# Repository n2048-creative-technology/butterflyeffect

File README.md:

# butterflyeffect

An art-installation project built around small ESP32-S3 "leaf" PCBs: each
leaf carries a radar presence sensor and a TFT display that reacts with a
glitch/text effect. Includes the PCB design (KiCad, three board revisions),
two firmware variants, and a source poem ("poetry monitors butterfly.pdf")
that the TFT glitch text is drawn from.

**Status: messy / in-progress.** This repo is committed close to how it sits
on the author's disk — see "Known issues" below before relying on it as a
clean starting point.

## What's in here

- **`PCB/leaf/`, `PCB/leaf2/`, `PCB/leaf3/`** — three KiCad project revisions
  for the same "leaf" board (ESP32-S6/S3 module, per `esp32-s3-leaf.kicad_sch`
  at the repo root). `leaf3` is the newest revision judging by file
  timestamps; `leaf`/`leaf2` look like earlier iterations kept for reference.
  Each folder also has a `production/` subfolder with JLCPCB-ready gerbers,
  BOM and pick-and-place files, plus a `*-backups/` folder full of
  auto-save zips from KiCad — safe to ignore/delete, not source files.
- **`esp32-s3/`** — a fourth, separate KiCad PCB export (gerbers + production
  files only, no schematic source committed alongside it) — likely an older
  or alternate board revision. Not clearly connected to `PCB/leaf*` from the
  file layout alone.
- **`code/esp32-s3-radar-test/`** — PlatformIO project reading an RD-03D
  mmWave presence/distance radar module over UART (`RD03D.h/.cpp`).
- **`code/esp32-s3-tft-display/`** — PlatformIO project driving a TFT
  display (via `TFT_eSPI`) with a scrolling/glitching text effect —
  `GLITCH_PERCENT`, `FRAME_DELAY_MS`, and the displayed text are `#define`d
  at the top of `leafs/src/main.cpp` and `code/esp32-s3-tft-display/src/main.cpp`.
  Uses a RAM-framebuffer sprite for performance (see the comment block in
  `main.cpp` explaining why).
- **`leafs/`** — a third, PlatformIO-structured copy of the TFT glitch
  firmware (`include/User_Setup.h` for `TFT_eSPI` pin config). Appears to be
  the "current" leaf firmware; unclear how it differs from
  `code/esp32-s3-tft-display/` without a diff.
- **`3dmodels/wings.scad`** — OpenSCAD source for a mechanical "wings" part.
- **`poetry monitors butterfly.pdf`** — the source text the glitch display
  renders excerpts of.

## Hardware

- ESP32-S3 module (per `esp32-s3-leaf.kicad_sch` / the `leaf` PCB silkscreen)
- RD-03D mmWave radar module (UART, 256000 baud) for the radar-test firmware
- A TFT display wired for `TFT_eSPI` (pinout is in `leafs/include/User_Setup.h`
  — check it before wiring a display, it is not documented here separately)
- Custom "leaf" PCB (KiCad projects above) carrying the ESP32-S3 and
  supporting components

No end-to-end wiring diagram tying the radar + display + leaf PCB into one
finished device exists in this repo — piece it together from the two
firmware projects' pin `#define`s and the KiCad schematic.

## Build & flash

Both firmware projects use PlatformIO:

```bash
cd code/esp32-s3-radar-test   # or code/esp32-s3-tft-display, or leafs/
pio run
pio run -t upload
pio device monitor
```

## Known issues

- **Three near-duplicate PCB revisions** (`PCB/leaf`, `PCB/leaf2`, `PCB/leaf3`)
  and a fourth unrelated-looking one (`esp32-s3/`) are committed side by
  side with no changelog explaining what changed between them. Before
  fabricating, diff the schematics or ask the author which is current
  (`leaf3` is the most recently modified).
- **KiCad auto-save backup zips are committed** (`*-backups/*.zip`, dozens
  of them, several MB each) — these bloat the repo and aren't needed to
  build the board; the checked-in `.kicad_pcb`/`.kicad_sch` files are the
  actual source of truth.
- **Two copies of the TFT glitch firmware** (`code/esp32-s3-tft-display/`
  and `leafs/`) with no documented relationship between them.
- No top-level wiring diagram or bill of materials tying the radar sensor,
  display, and PCB together into one buildable device.

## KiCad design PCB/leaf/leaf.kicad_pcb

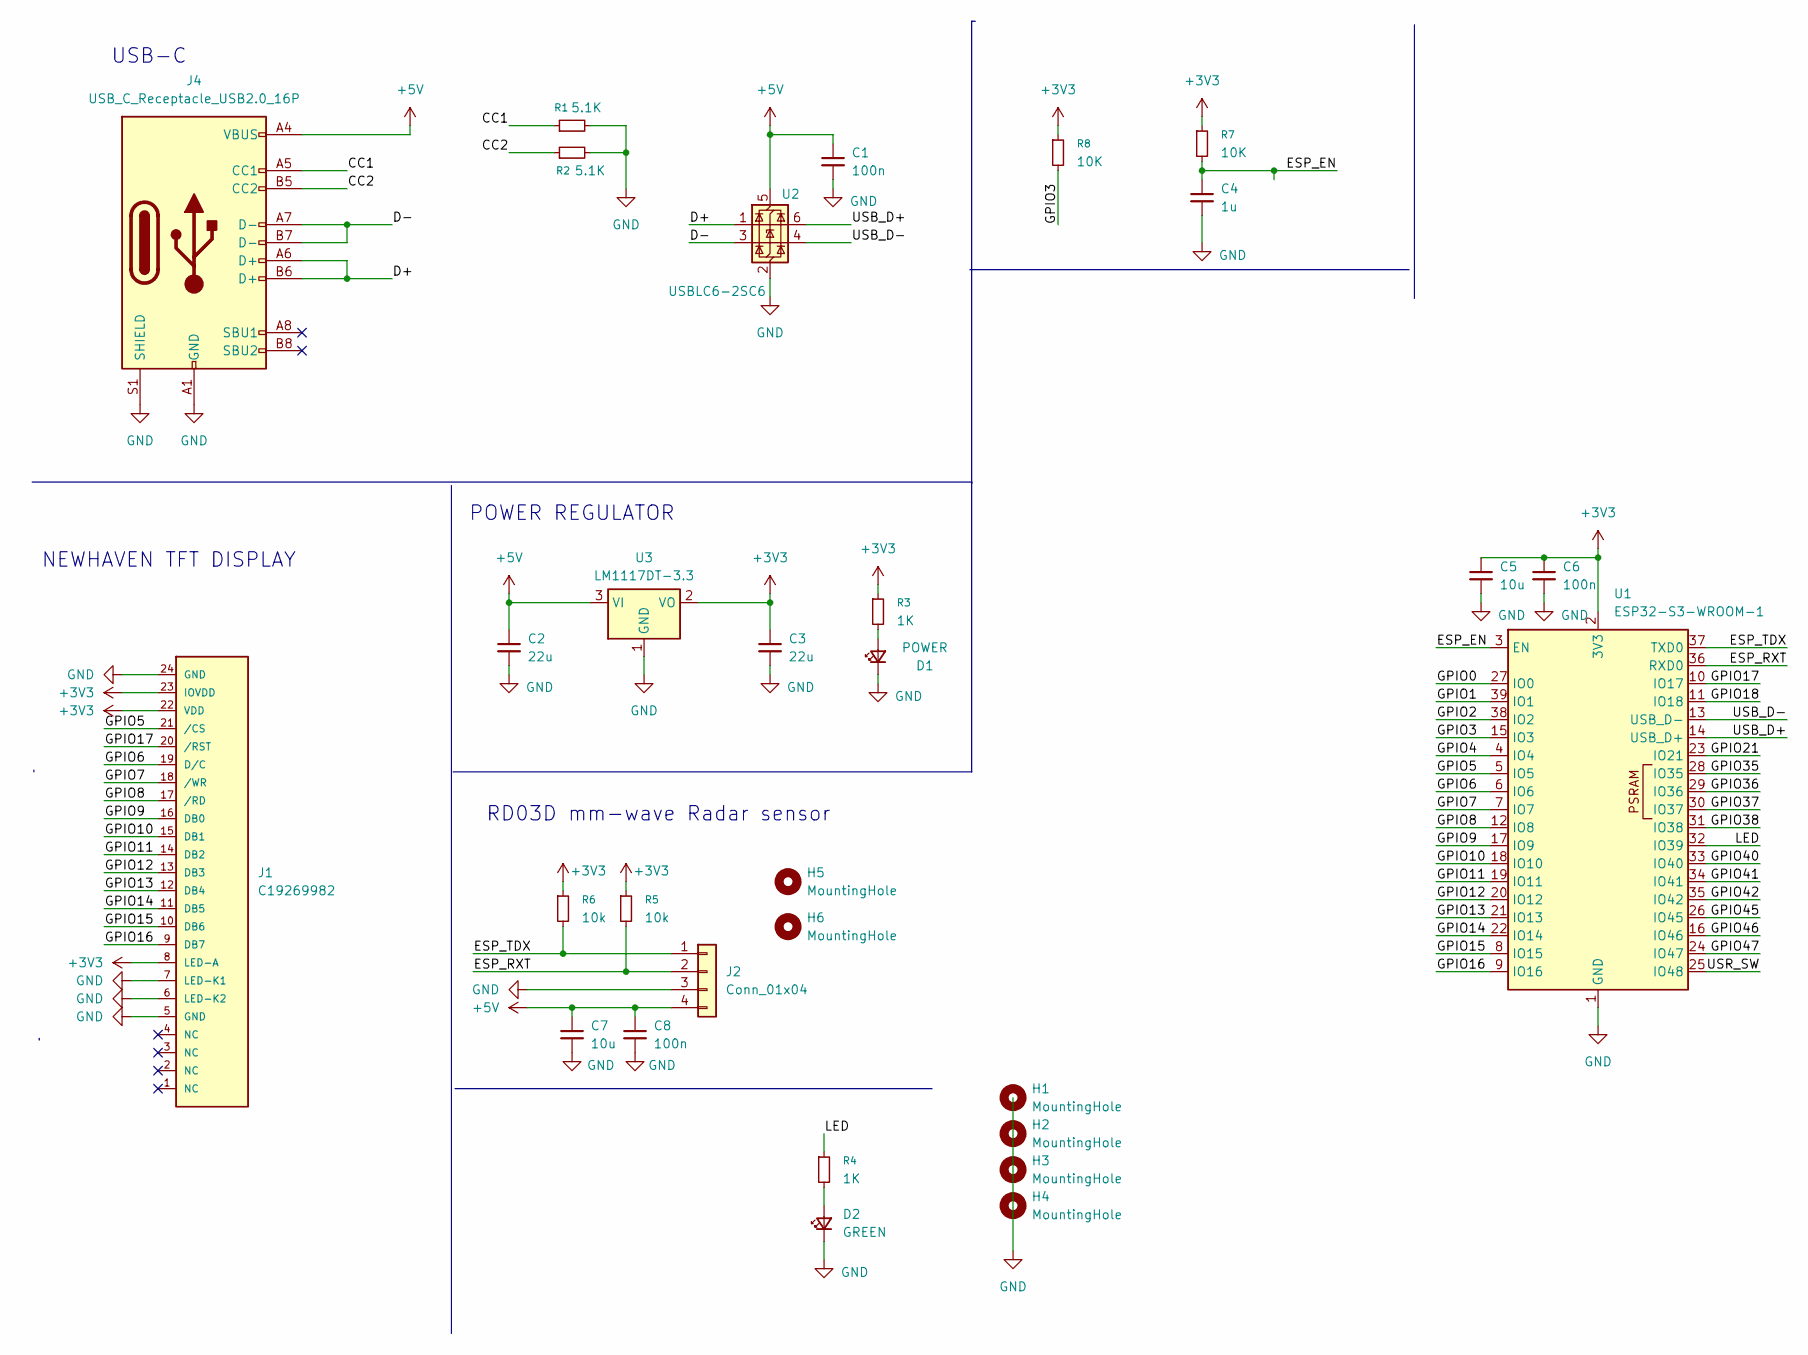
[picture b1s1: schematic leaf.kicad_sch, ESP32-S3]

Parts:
C1, C6, C8: 100n; C_01005_0402Metric_Pad0.57x0.30mm_HandSolder
C2, C3: 22u; C_1210_3225Metric
C4: 1u; C_0603_1608Metric
C5, C7: 10u; C_0603_1608Metric
D1: POWER; LED_0603_1608Metric
D2: GREEN; LED_0603_1608Metric
H1, H2, H3, H4: MountingHole; MountingHole_4.3mm_M4_ISO14580_Pad
H5, H6: MountingHole; MountingHole_2.2mm_M2_ISO7380_Pad
J1: C19269982; Molex_502244-2430_1x24-1MP_P0.5mm_Horizontal
J2: Conn_01x04; Molex_PicoBlade_53261-0471_1x04-1MP_P1.25mm_Horizontal
J4: USB_C_Receptacle_USB2.0_16P; USB_C_Receptacle_GCT_USB4105-xx-A_16P_TopMnt_Horizontal
R1, R2: 5.1K; R_0402_1005Metric_Pad0.72x0.64mm_HandSolder
R3, R4: 1K; R_0402_1005Metric_Pad0.72x0.64mm_HandSolder
R5, R6: 10k; R_0402_1005Metric_Pad0.72x0.64mm_HandSolder
R7, R8: 10K; R_0402_1005Metric_Pad0.72x0.64mm_HandSolder
U1: ESP32-S3-WROOM-1
U2: USBLC6-2SC6; SOT-23-6
U3: LM1117DT-3.3; TO-252-3_TabPin2

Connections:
+3V3: C3.1, C5.1, C6.1, J1.8 (LED-A), J1.22 (VDD), J1.23 (IOVDD), R3.1, R5.1, R6.1, R7.1, R8.1, U1.2 (3V3), U3.2 (VO)
+5V: C1.1, C2.1, C7.1, C8.1, J2.4, J4.A4 (VBUS), J4.A9 (VBUS), J4.B4 (VBUS), J4.B9 (VBUS), U2.5 (VBUS), U3.3 (VI)
/CC1: J4.A5 (CC1), R1.1
/CC2: J4.B5 (CC2), R2.1
/D+: J4.A6 (D+), J4.B6 (D+), U2.1 (I/O1)
/D-: J4.A7 (D-), J4.B7 (D-), U2.3 (I/O2)
/ESP_EN: C4.1, R7.2, U1.3 (EN)
/ESP_RXT: J2.2, R5.2, U1.36 (RXD0)
/ESP_TDX: J2.1, R6.2, U1.37 (TXD0)
/GPIO0: U1.27 (IO0)
/GPIO1: U1.39 (IO1)
/GPIO2: U1.38 (IO2)
/GPIO3: R8.2, U1.15 (IO3)
/GPIO4: U1.4 (IO4)
/GPIO5: J1.21 (/CS), U1.5 (IO5)
/GPIO6: J1.19 (D/C), U1.6 (IO6)
/GPIO7: J1.18 (/WR), U1.7 (IO7)
/GPIO8: J1.17 (/RD), U1.12 (IO8)
/GPIO9: J1.16 (DB0), U1.17 (IO9)
/GPIO10: J1.15 (DB1), U1.18 (IO10)
/GPIO11: J1.14 (DB2), U1.19 (IO11)
/GPIO12: J1.13 (DB3), U1.20 (IO12)
/GPIO13: J1.12 (DB4), U1.21 (IO13)
/GPIO14: J1.11 (DB5), U1.22 (IO14)
/GPIO15: J1.10 (DB6), U1.8 (IO15)
/GPIO16: J1.9 (DB7), U1.9 (IO16)
/GPIO17: J1.20 (/RST), U1.10 (IO17)
/GPIO18: U1.11 (IO18)
/GPIO21: U1.23 (IO21)
/GPIO35: U1.28 (IO35)
/GPIO36: U1.29 (IO36)
/GPIO37: U1.30 (IO37)
/GPIO38: U1.31 (IO38)
/GPIO40: U1.33 (IO40)
/GPIO41: U1.34 (IO41)
/GPIO42: U1.35 (IO42)
/GPIO45: U1.26 (IO45)
/GPIO46: U1.16 (IO46)
/GPIO47: U1.24 (IO47)
/LED: R4.1, U1.32 (IO39)
/USB_D+: U1.14 (USB_D+), U2.6 (I/O1)
/USB_D-: U1.13 (USB_D-), U2.4 (I/O2)
/USR_SW: U1.25 (IO48)
GND: C1.2, C2.2, C3.2, C4.2, C5.2, C6.2, C7.2, C8.2, D1.1 (K), D2.1 (K), J1.5 (GND), J1.6 (LED-K2), J1.7 (LED-K1), J1.24 (GND), J1.MP, J2.3, J2.MP, J4.A1 (GND), J4.A12 (GND), J4.B1 (GND), J4.B12 (GND), J4.S1 (SHIELD), R1.2, R2.2, U1.1 (GND), U1.40 (GND), U1.41 (GND), U2.2 (GND), U3.1 (GND)
unnamed: D1.2 (A), R3.2
unnamed: D2.2 (A), R4.2

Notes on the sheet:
NEWHAVEN TFT DISPLAY
USB-C
POWER REGULATOR
RD03D mm-wave Radar sensor

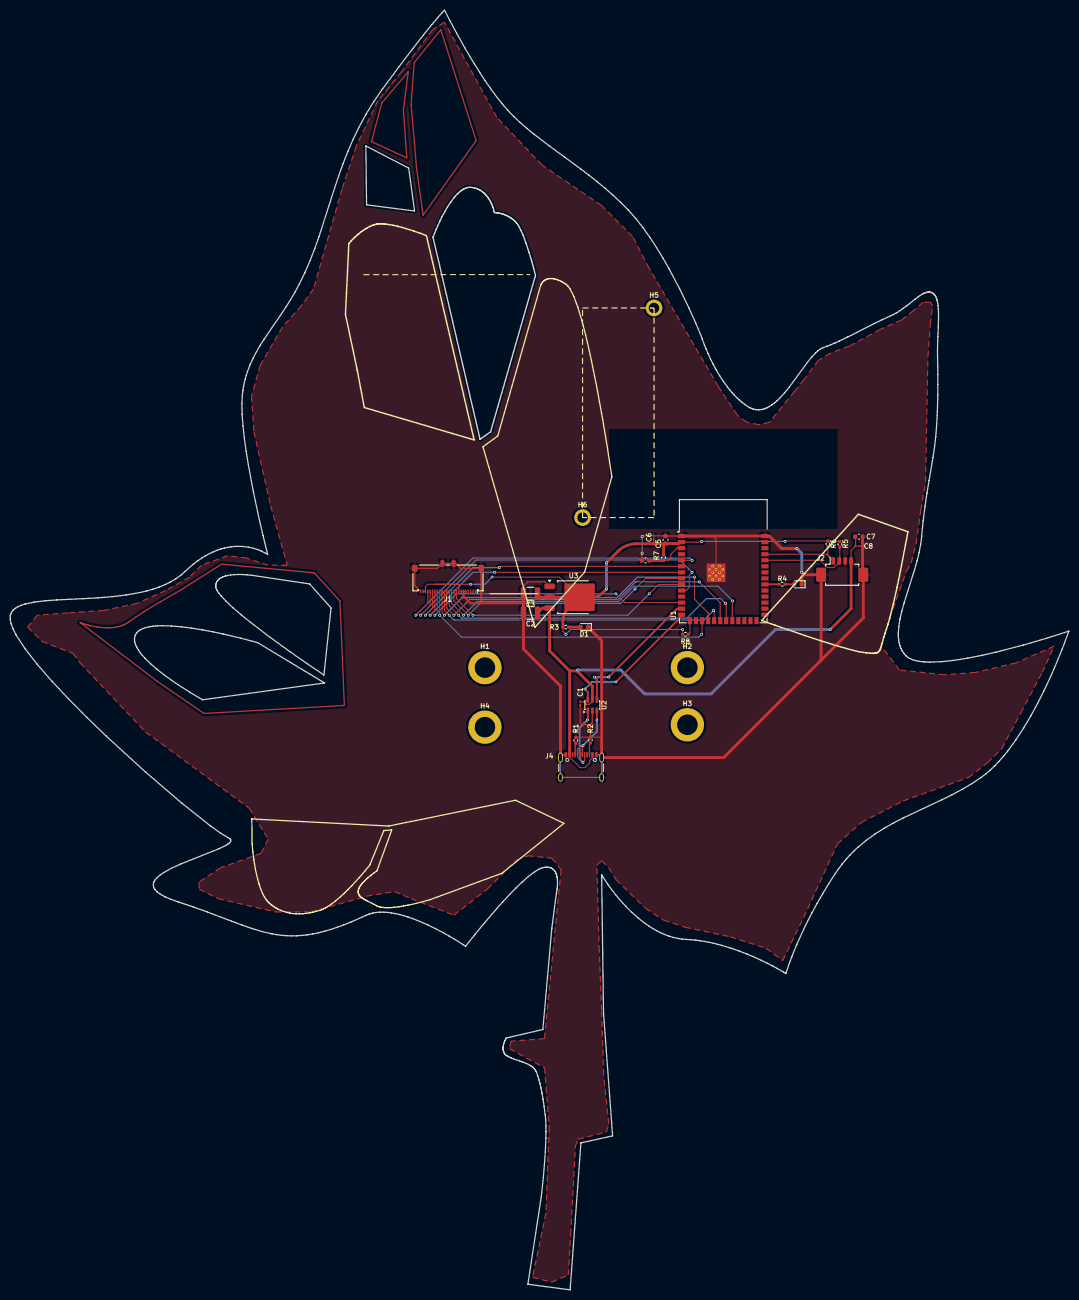
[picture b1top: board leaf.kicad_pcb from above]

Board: 2 copper layers, 222.3 x 268.6 mm, 30 parts (0 on the bottom side), 29 nets.

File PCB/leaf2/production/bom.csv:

Designator,Footprint,Quantity,Value,LCSC Part #
"C1, C6, C8",01005,3,100n,
"C2, C3",1210,2,22u,
C4,0603,1,1u,
"C5, C7",0603,2,10u,
D1,0603,1,POWER,
D2,0603,1,GREEN,
J1,Molex_502244-2430_1x24-1MP_P0.5mm_Horizontal,1,C19269982,
J2,Molex_PicoBlade_53261-0471_1x04-1MP_P1.25mm_Horizontal,1,Conn_01x04,
J4,USB_C_Receptacle_GCT_USB4105-xx-A_16P_TopMnt_Horizontal,1,USB_C_Receptacle_USB2.0_16P,
"R1, R2",0402,2,5.1K,
"R3, R4",0402,2,1K,
"R5, R6, R7, R8",0402,4,10k,
U1,ESP32-S3-WROOM-1,1,ESP32-S3-WROOM-1,
U2,SOT-23-6,1,USBLC6-2SC6,
U3,TO-252-3_TabPin2,1,LM1117DT-3.3,

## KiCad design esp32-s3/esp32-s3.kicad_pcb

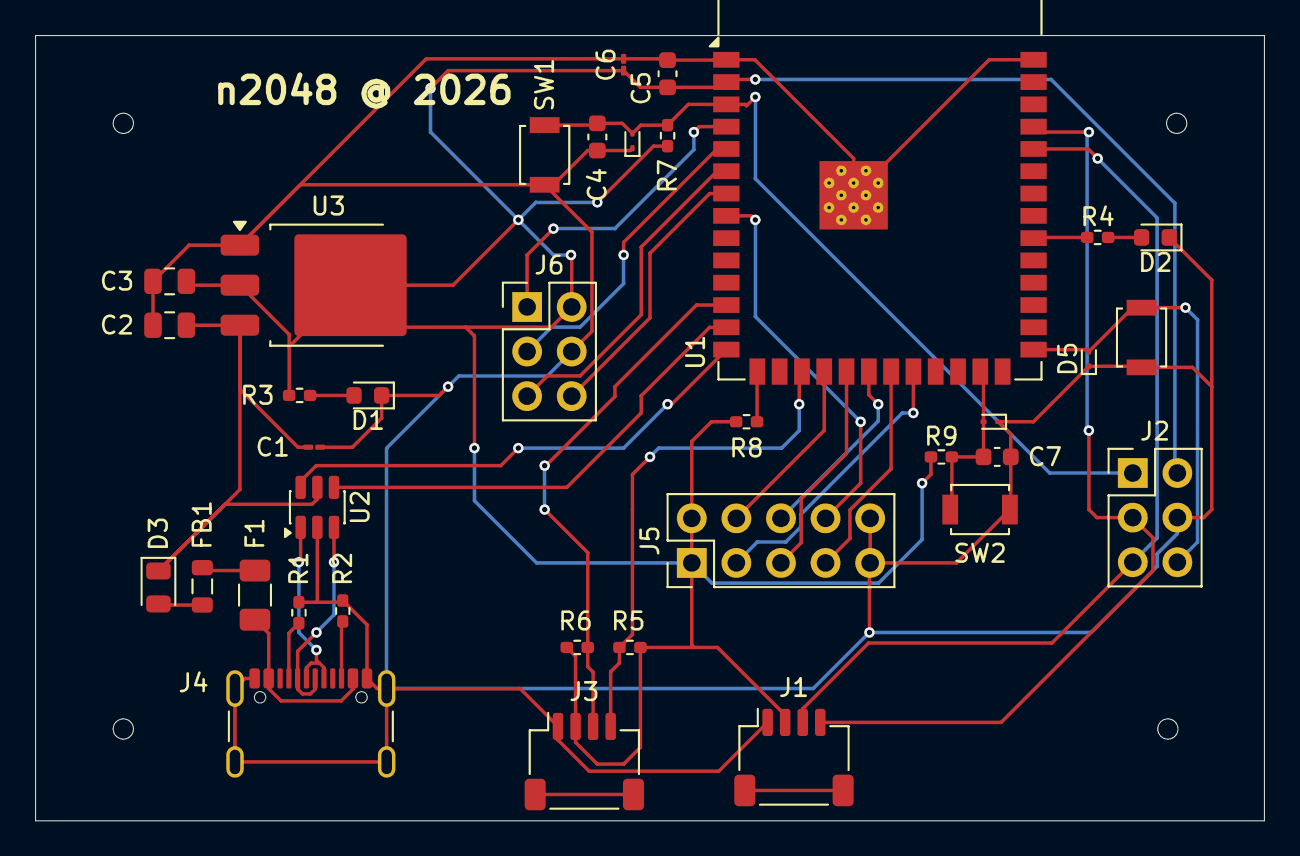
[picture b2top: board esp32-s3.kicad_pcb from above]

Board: 2 copper layers, 70.0 x 44.7 mm, 40 parts (0 on the bottom side), 33 nets.

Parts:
C1, C6: 100n; C_01005_0402Metric_Pad0.57x0.30mm_HandSolder
C2, C3: 22u; C_0805_2012Metric
C4, C7: 1u; C_0603_1608Metric
C5: 10u; C_0603_1608Metric
D1: POWER; LED_0603_1608Metric
D2: GREEN; LED_0603_1608Metric
D3: 1N5817; D_0805_2012Metric
D4, D5, D6: ESD3.3; D_SOD-923
F1: Polyfuse 1A; Fuse_1206_3216Metric
FB1: BLM21PG220; L_0805_2012Metric
H1, H2, H3, H4: MountingHole; ToolingHole_1.152mm
J1, J3: Conn_01x04; JST_SH_SM04B-SRSS-TB_1x04-1MP_P1.00mm_Horizontal
J2, J6: Conn_02x03_Odd_Even; PinHeader_2x03_P2.54mm_Vertical
J4: USB_C_Receptacle_USB2.0_16P; USB_C_Receptacle_GCT_USB4105-xx-A_16P_TopMnt_Horizontal
J5: PIN 02x05; PinHeader_2x05_P2.54mm_Vertical
R1, R2: 5.1K; R_0402_1005Metric_Pad0.72x0.64mm_HandSolder
R3, R4: 1K; R_0402_1005Metric_Pad0.72x0.64mm_HandSolder
R5, R6: 2K2; R_0402_1005Metric_Pad0.72x0.64mm_HandSolder
R7, R8, R9: 10K; R_0402_1005Metric_Pad0.72x0.64mm_HandSolder
SW1: RESET; SW_SPST_B3U-1000P
SW2: USER_BTN; SW_SPST_B3U-1000P
SW3: BOOT; SW_SPST_B3U-1000P
U1: ESP32-S3-WROOM-1
U2: USBLC6-2SC6; SOT-23-6
U3: LM1117DT-3.3; TO-252-3_TabPin2

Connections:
+3V3: C3.1, C5.1, C6.1, J1.2, J2.2, J3.2, J5.1, J5.2, J6.2, R3.1, R5.1, R6.1, R7.1, R8.1, R9.1, U1.2 (3V3), U3.2 (VO)
+5V: C1.1, C2.1, D3.1 (K), U2.5 (VBUS), U3.3 (VI)
/CC1: J4.A5 (CC1), R1.1
/CC2: J4.B5 (CC2), R2.1
/CLK: J5.6, U1.20 (IO12)
/CS: J5.4, U1.18 (IO10)
/D+: J4.A6 (D+), J4.B6 (D+), U2.1 (I/O1)
/D-: J4.A7 (D-), J4.B7 (D-), U2.3 (I/O2)
/ESP_EN: C4.1, D4.2 (A2), J2.1, R7.2, SW1.2 (B), U1.3 (EN)
/ESP_RXT: J1.3, J2.5, U1.36 (RXD0)
/ESP_TDX: J1.4, J2.3, U1.37 (TXD0)
/GPIO0: D5.2 (A2), J2.6, SW3.2 (B), U1.27 (IO0)
/GPIO3: R8.2, U1.15 (IO3)
/GPIO4: J6.1, U1.4 (IO4)
/GPIO5: J6.3, U1.5 (IO5)
/GPIO6: J6.5, U1.6 (IO6)
/GPIO7: J6.6, U1.7 (IO7)
/IRQ: J5.8, U1.8 (IO15)
/LED: R4.1, U1.32 (IO39)
/MISO: J5.7, U1.21 (IO13)
/MOSI: J5.5, U1.19 (IO11)
/RESET: J5.3, U1.22 (IO14)
/SCL: J3.4, R5.2, U1.17 (IO9)
/SDA: J3.3, R6.2, U1.12 (IO8)
/USB_D+: U1.14 (USB_D+), U2.6 (I/O1)
/USB_D-: U1.13 (USB_D-), U2.4 (I/O2)
/USR_SW: C7.1, D6.2 (A2), R9.2, SW2.2 (B), U1.25 (IO48)
GND: C1.2, C2.2, C3.2, C4.2, C5.2, C6.2, C7.2, D1.1 (K), D2.1 (K), D4.1 (A1), D5.1 (A1), D6.1 (A1), J1.1, J2.4, J3.1, J4.A1 (GND), J4.A12 (GND), J4.B1 (GND), J4.B12 (GND), J4.S1 (SHIELD), J5.9, J5.10, J6.4, R1.2, R2.2, SW1.1 (A), SW2.1 (A), SW3.1 (A), U1.1 (GND), U1.40 (GND), U1.41 (GND), U2.2 (GND), U3.1 (GND)
unnamed: D1.2 (A), R3.2
unnamed: D2.2 (A), R4.2
unnamed: D3.2 (A), FB1.2
unnamed: F1.1, J4.A4 (VBUS), J4.A9 (VBUS), J4.B4 (VBUS), J4.B9 (VBUS)
unnamed: F1.2, FB1.1

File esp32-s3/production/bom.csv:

Designator,Footprint,Quantity,Value,LCSC Part #
"C1, C6",01005,2,100n,
"C2, C3",0805,2,22u,
"C4, C7",0603,2,1u,
C5,0603,1,10u,
D1,0603,1,POWER,
D2,0603,1,GREEN,
D3,0805,1,1N5817,
"D4, D5, D6",D_SOD-923,3,ESD3.3,
F1,1206,1,Polyfuse 1A,
FB1,0805,1,BLM21PG220,
"J1, J3",JST_SH_SM04B-SRSS-TB_1x04-1MP_P1.00mm_Horizontal,2,Conn_01x04,
"J2, J6",PinHeader_2x03_P2.54mm_Vertical,2,Conn_02x03_Odd_Even,
J4,USB_C_Receptacle_GCT_USB4105-xx-A_16P_TopMnt_Horizontal,1,USB_C_Receptacle_USB2.0_16P,
J5,PinHeader_2x05_P2.54mm_Vertical,1,PIN 02x05,
"R1, R2",0402,2,5.1K,
"R3, R4",0402,2,1K,
"R5, R6",0402,2,2K2,
"R7, R8, R9",0402,3,10K,
SW1,SW_SPST_B3U-1000P,1,RESET,
SW2,SW_SPST_B3U-1000P,1,USER_BTN,
SW3,SW_SPST_B3U-1000P,1,BOOT,
U1,ESP32-S3-WROOM-1,1,ESP32-S3-WROOM-1,
U2,SOT-23-6,1,USBLC6-2SC6,
U3,TO-252-3_TabPin2,1,LM1117DT-3.3,

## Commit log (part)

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2026-06-12 new folder structure structure
2026-06-19 functional text glitch effect
2026-06-19 add radar sensor to determine glitch intensity
2026-06-19 font size
2026-06-19 mechanical wings design
